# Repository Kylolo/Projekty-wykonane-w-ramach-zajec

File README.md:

# Projekty-wykonane-w-ramach-zajec

Zbiór różnych projektów wykonanych głównie na 2 roku studiów, ale niektóre są z innych lat.

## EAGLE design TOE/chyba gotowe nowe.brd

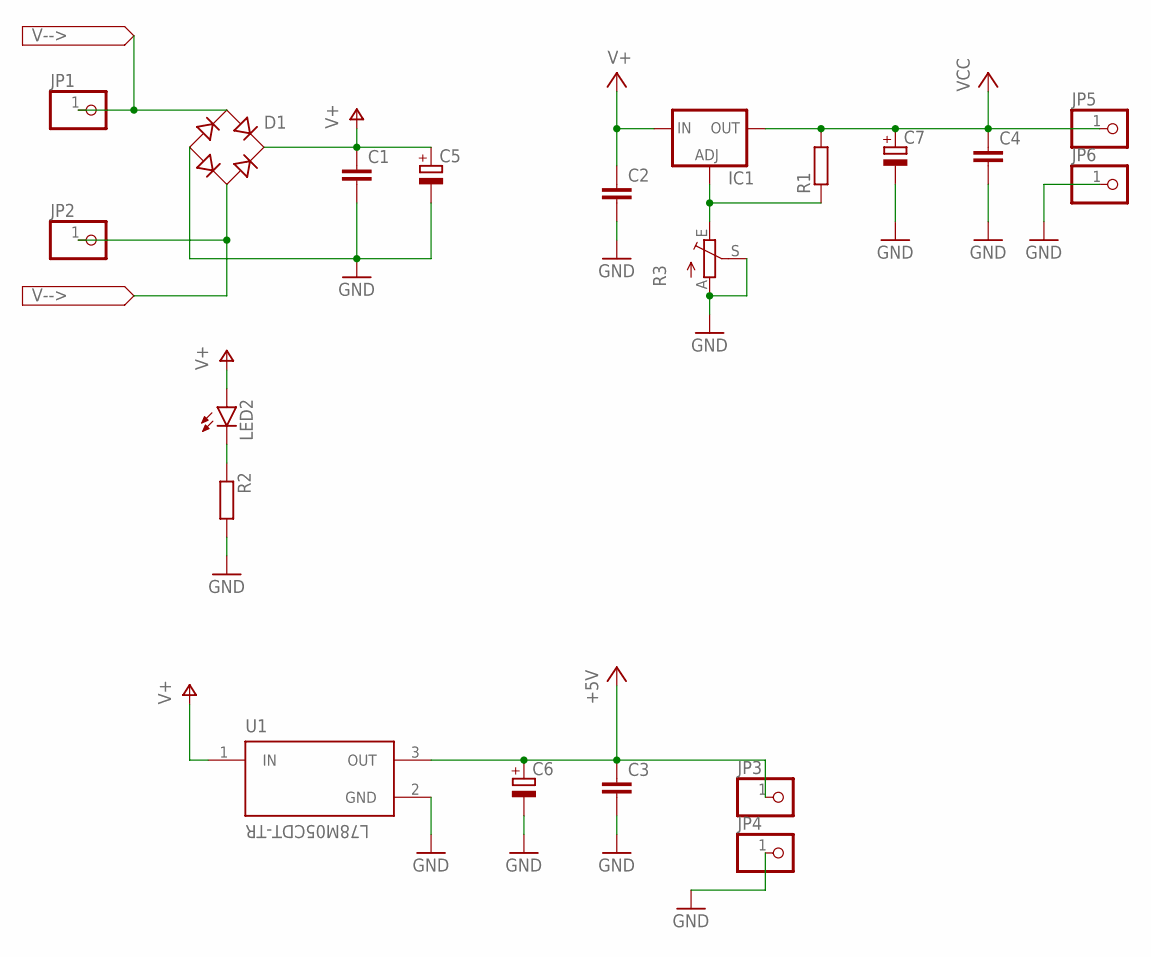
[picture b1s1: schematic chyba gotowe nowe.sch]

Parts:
C1, C2, C3, C4: C-EUC1206; C1206
C5, C6, C7: CPOL-EUTT5D10; TT5D10
D1: RECTIFIER-RB1A; RB1A
IC1: LM317MSTT3; SOT223
JP1, JP2, JP3, JP4, JP5, JP6: PINHD-1X1; 1X01
LED2: LEDSMT1206; 1206
R1, R2: R-EU_R1206; R1206
R3: TRIM_EU-PT10; PT-10
U1: L78M05CDT-TR; VREG_L78M05CDT-TR

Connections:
+5V: C3.1, C6.+, JP3.1, U1.3 (OUT)
GND: C1.2, C2.2, C3.2, C4.2, C5.-, C6.-, C7.-, D1.-, JP4.1, JP6.1, R2.2, R3.A, R3.S, U1.2 (GND)
unnamed: LED2.C, R2.1
unnamed: D1.AC1, JP1.1
unnamed: D1.AC2, JP2.1
unnamed: IC1.1 (ADJ), R1.1, R3.E
V+: C1.1, C2.1, C5.+, D1.+, IC1.3 (IN), LED2.A, U1.1 (IN)
VCC: C4.1, C7.+, IC1.4 (OUT), JP5.1, R1.2

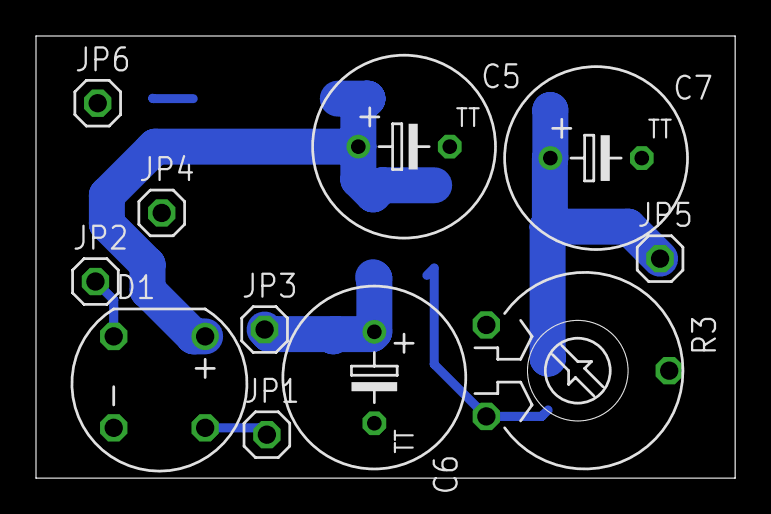
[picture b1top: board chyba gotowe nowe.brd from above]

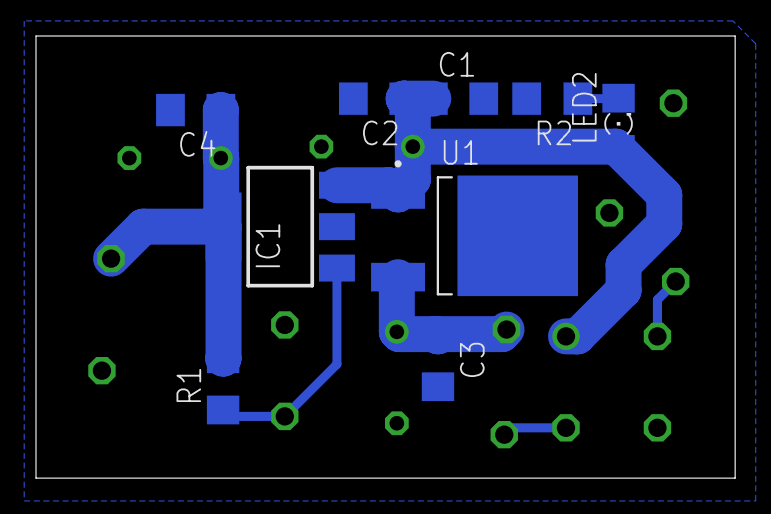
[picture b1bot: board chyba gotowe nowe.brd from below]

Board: 2 copper layers, 38.8 x 24.6 mm, 20 parts (9 on the bottom side), 8 nets.

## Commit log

2026-03-03 Create Opis projektu
